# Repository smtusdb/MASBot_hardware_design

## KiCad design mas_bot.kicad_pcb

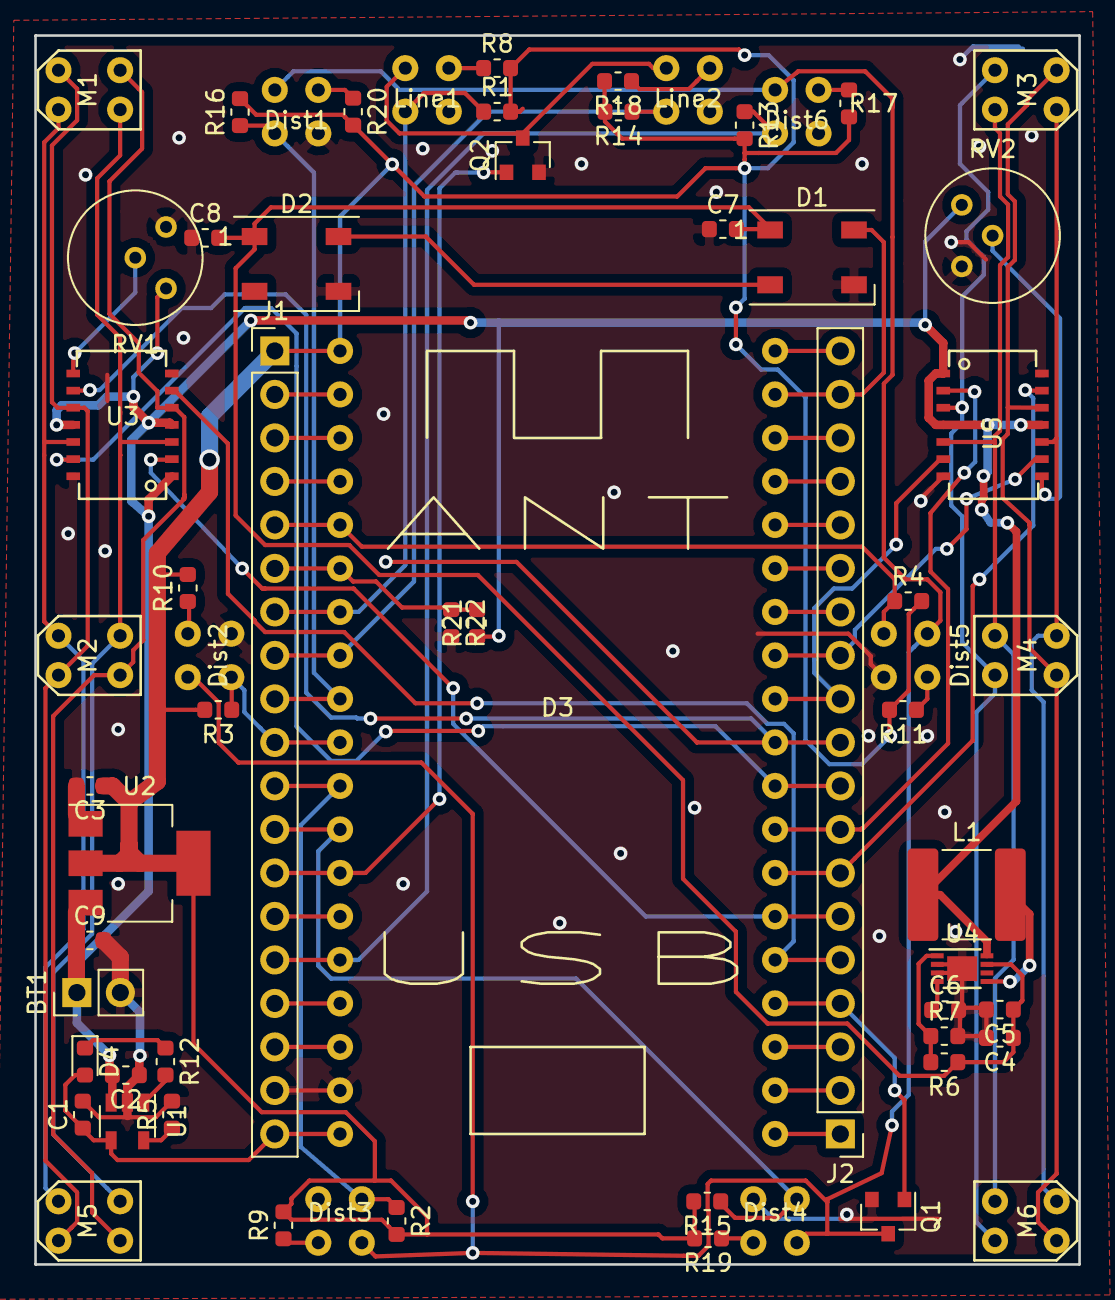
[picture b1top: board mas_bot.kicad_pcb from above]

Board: 2 copper layers, 61.0 x 71.8 mm, 62 parts (0 on the bottom side), 67 nets.

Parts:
BT1: Battery_Li-Po; PinHeader_1x02_P2.54mm_Vertical
C1, C2: 4.7u; C_0603_1608Metric
C3, C5: 10u; C_0603_1608Metric
C4: 0.1u; C_0603_1608Metric
C6: 4.7 u; C_0603_1608Metric
C7, C8: 15pF; C_0603_1608Metric
C9: C_Small; C_0603_1608Metric
D1, D2: WS2812B; LED_WS2812B_PLCC4_5.0x5.0mm_P3.2mm
D3: ESP32_board; ESP32_board_36pin
D4: LED; LED_0603_1608Metric
Dist1, Dist2, Dist3, Dist4, Dist5, Dist6: QRE1113; qre1113_vert
J1, J2: Conn_01x19_Male; PinHeader_1x19_P2.54mm_Vertical
L1: 4.7uH; C_2220_5650Metric
Line1, Line2: QRE1113; qre1113_vert
M1, M2, M3, M4, M5, M6: micro_srpper
Q1, Q2: Q_NPN_BCE; SOT-23
R1, R2, R3, R4, R13, R14, R15, R16: 2 Kom; R_0603_1608Metric
R5, R21, R22: ?; R_0603_1608Metric
R6: 976 Kom; R_0603_1608Metric
R7, R8, R9, R10, R11, R17, R18, R19, R20: 309 Kom; R_0603_1608Metric
R12: 470R; R_0603_1608Metric
RV1, RV2: 2KOm; Potentiometer_Bourns_3339H_Vertical
U1: MCP73831-2-OT; SOT-23-5
U2: LM1117-3.3; SOT-223-3_TabPin2
U3, U5: LB1836M
U4: MCP1640CMC; DFN-8-1EP_3x2mm_P0.5mm_EP1.75x1.45mm

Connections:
+3V3: C3.1, D3.38, J1.1, R1.2, R2.2, R3.2, R4.2, R8.2, R9.2, R10.2, R11.2, R13.2, R14.2, R15.2, R16.2, R17.2, R18.2, R19.2, R20.2, U2.2
+3V8: BT1.1, C2.2, C9.1, L1.1, R21.1, RV1.3, RV2.3, U1.3, U2.3, U3.1, U3.4, U3.11, U4.8, U5.1, U5.4, U5.11
+5V: C4.1, C5.1, C7.2, C8.2, D1.1, D2.1, R6.1, U4.7
/Dist: Dist1.2, Dist2.2, Dist3.2, Dist4.2, Dist5.2, Dist6.2, Q1.3
/IR_RX1: D3.30, Dist1.3, J1.9, R16.1
/IR_RX2: D3.29, Dist2.3, J1.10, R3.1
/IR_RX3: D3.28, Dist3.3, J1.11, R2.1
/IR_RX4: D3.27, Dist4.3, J1.12, R15.1
/IR_RX5: D3.34, Dist5.3, J1.5, R4.1
/IR_RX6: D3.24, Dist6.3, J1.15, R13.1
/IR_TX: D3.16, J2.4, Q1.1
/Line: Line1.2, Line2.2, Q2.3
/Line_tx: D3.26, J1.13, Q2.1
/M1_IN1: D3.14, J2.6, U3.2
/M1_IN2: D3.15, J2.5, U3.6
/M1_IN3: D3.11, J2.9, U3.13
/M1_IN4: D3.10, J2.10, U3.9
/M2_IN1: D3.12, J2.8, U5.2
/M2_IN2: D3.9, J2.11, U5.6
/M2_IN3: D3.13, J2.7, U5.13
/M2_IN4: D3.8, J2.12, U5.9
/RGBleds: D1.4, D3.2, J2.18
/line_in1: D3.32, J1.7, Line1.3, R1.1
/line_in2: D3.31, J1.8, Line2.3, R14.1
GND: BT1.2, C1.2, C2.1, C3.2, C4.2, C5.2, C6.2, C7.1, C8.1, C9.2, D1.3, D2.3, D3.21, Dist1.4, Dist2.4, Dist3.4, Dist4.4, Dist5.4, Dist6.4, J1.18, Line1.4, Line2.4, Q1.2, Q2.2, R5.2, R7.2, R22.2, RV1.1, RV2.1, U1.2, U2.1, U3.7, U3.14, U4.2, U4.3, U4.9, U5.7, U5.14
unnamed: C6.1, U4.4
unnamed: D1.2, D2.4
unnamed: D3.1, J2.19
unnamed: D3.3, J2.17
unnamed: D3.4, J2.16
unnamed: D3.5, J2.15
unnamed: D3.6, J2.14
unnamed: D3.7, J2.13
unnamed: D3.17, J2.3
unnamed: D3.18, J2.2
unnamed: D3.19, J2.1
unnamed: D3.22, J1.17
unnamed: D3.23, J1.16
unnamed: D3.25, J1.14
unnamed: D3.33, J1.6, R21.2, R22.1
unnamed: D3.35, J1.4
unnamed: D3.36, J1.3
unnamed: D3.37, J1.2
unnamed: D4.1, R12.1
unnamed: Dist1.1, R20.1
unnamed: Dist2.1, R10.1
unnamed: Dist3.1, R9.1
unnamed: Dist4.1, R19.1
unnamed: Dist5.1, R11.1
unnamed: Dist6.1, R17.1
unnamed: L1.2, U4.5
unnamed: Line1.1, R8.1
unnamed: Line2.1, R18.1
unnamed: M1.1, M2.2, M5.2, U3.10
unnamed: M1.2, M2.1, M5.1, U3.12
unnamed: M1.3, M2.4, M5.4, U3.3
unnamed: M1.4, M2.3, M5.3, U3.5
unnamed: M3.1, M4.2, M6.2, U5.10
unnamed: M3.2, M4.1, M6.1, U5.12
unnamed: M3.3, M4.4, M6.4, U5.3
unnamed: M3.4, M4.3, M6.3, U5.5
unnamed: R5.1, U1.5
unnamed: R6.2, R7.1, U4.1
unnamed: R12.2, U1.1
unnamed: RV1.2, U3.8
unnamed: RV2.2, U5.8
VDD: C1.1, D3.20, D4.2, J1.19, U1.4

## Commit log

2019-03-31 publish
2019-03-31 added license
